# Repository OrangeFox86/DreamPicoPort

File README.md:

# DreamPicoPort (formally DreamcastControllerUsbPico)

Using a Raspberry Pi Pico, DreamPicoPort enables USB interfacing with a Dreamcast or its controllers and peripherals, functioning in either host mode or client mode as depicted below.

Refer to [these instructions](https://github.com/OrangeFox86/DreamPicoPort/wiki/*-Host-Mode-Installation-Guide-(for-use-with-Flycast)) in order to use this with [Hollycast](https://github.com/OrangeFox86/Hollycast) or [flycast](https://github.com/flyinghead/flycast).

| Host Mode | Client Mode |
| -------- | ------- |
|  |  |

This platform may easily be forked and adapted for other interfacing needs. Feel free to do so under the conditions of the supplied [LICENSE.md](LICENSE.md).

Refer to the [releases](https://github.com/OrangeFox86/DreamPicoPort/releases) page for current progress. Refer to the [issues](https://github.com/OrangeFox86/DreamPicoPort/issues) tab for things left to be implemented and known bugs.

---

# General Disclaimer

Proceed at your own risk! I am not liable for any damage that may occur due to the use of any provided schematics, firmware, or any other recommendations made within this project (see [LICENSE.md](LICENSE.md)). There is risk of damage to any attached hardware (ex: USB port, Dreamcast peripheral, or Dreamcast) if circuitry is improperly handled.

---

# Quick Installation Guide

These instructions have been moved to [the wiki](https://github.com/OrangeFox86/DreamPicoPort/wiki/Installation-Guide).

# Build Instructions (for Linux and Windows)

If running under Windows, install [WSL](https://docs.microsoft.com/en-us/windows/wsl/install) and your desired flavor of Linux. I recommend using Ubuntu 22.04 as that is what I have used for development. Then the steps below may be run within your WSL instance.

1. Install git, cmake, and gcc-arm-none-eabi compiler by running the following commands
```bash
sudo apt update
sudo apt -y install git cmake gcc-arm-none-eabi
```

2. (optional) In order to run and debug tests, install standard gcc compilers and gdb by running the following
```bash
sudo apt -y install build-essential gdb
```

3. Clone this repo then cd into the created directory
```bash
git clone https://github.com/Tails86/DreamPicoPort.git
cd DreamPicoPort
```

4. Pull down the pico SDK (this project now uses a fork of the SDK - it will no longer compile under the standard SDK)
```bash
git submodule update --recursive --init
```
Hint: if you have issues building, the easiest way to correct any submodule synchronization issue is to delete the `ext/pico-sdk` directory (ex: `rm -rf ext/pico-sdk`), restore the directory `git restore ext/pico-sdk`, and then re-run the above submodule update command.

5. (optional) Build and run tests - this runs core lib unit tests locally
```bash
./run_tests.sh
```

6. Execute the build script
```bash
./build.sh
```

After build completes, binaries should be located under `dist/`. Pre-built release binaries may be found [here](https://github.com/OrangeFox86/DreamPicoPort/releases).

This project may be opened in vscode. In vscode, the default shortcut `ctrl+shift+b` will build the project. The default shortcut `F5` will run tests with gdb for local debugging. Open the terminal tab after executing tests with debugging to see the results.

---

# Maple Bus Implementation

The Maple Bus is a serial communications protocol which Dreamcast uses to communicate with controllers and other peripherals. Refer to documentation [here](https://dreamcast.wiki/Maple_bus) for general information about the Maple Bus.

## Why the RP2040/RP2350 are Game Changers for Emulating Communication Protocols

To emulate a bespoke communication protocol such as the Maple Bus on an MCU, one would usually either need to add extra hardware or bit bang the interface. This is not true with the RP2040/RP2350 and their PIO. Think of it as several extra small processors on the side using a special machine language purpose-built for handling I/O. This means communication can be offloaded to the PIO and only check on them after an interrupt is activated or a timeout has elapsed. Check out [maple_in.pio](src/hal/MapleBus/maple_in.pio) and [maple_out.pio](src/hal/MapleBus/maple_out.pio) to see the PIO code.

Luckily, the RP2040/RP2350 come with 2 PIO blocks each with 4 separate state machines. This means that the RP2040/RP2350 can easily emulate 4 separate controller interfaces, each at full speed!

## Interfacing with the PIO State Machines

The [MapleBus class](src/hal/MapleBus/MapleBus.hpp) operates as the interface between the microcontroller's code and the PIO state machines, [maple_in.pio](src/hal/MapleBus/maple_in.pio) and [maple_out.pio](src/hal/MapleBus/maple_out.pio).

Using 2 separate PIO blocks for reading and writing is necessary because each PIO block can only hold up to 32 instructions, and this interface is too complex to fit both read and write into a single block. Therefore, the write state machine is completely stopped before starting the read state machine for the targeted bus. Switching state machines is fast enough that there shouldn't be a problem. Testing showed the handoff always occurs within 1 microsecond after bringing the bus back to neutral. A device on the Maple Bus starts responding some time after 50 microseconds from the point of the bus going neutral after an end sequence. This ensures that a response is always captured.

The following lays out the phases of the state machine handled within the MapleBus class.

### PIO Data Handoff

When the write method is called, data is loaded into the Direct Memory Access (DMA) channel designated for use with the maple_out state machine in the MapleBus instance. The DMA will automatically load data onto the TX FIFO of the output PIO state machine so it won't stall waiting for more data.

The first 32-bit word loaded onto the output DMA is how many transmission bits will follow. In order for the state machine to process things properly, `(x - 8) % 32 == 0 && x >= 40` must be true where x is the value of that first 32-bit word i.e. every word is 32 bits long and at least a frame word (32 bits) plus a CRC byte (8 bits) are in the packet. This value needs to be loaded with byte order flipped because byte swap is enabled in the DMA so that all other words are written in the correct byte order. The rest of the data loaded into DMA is the entirety of a single packet as a uint32 array. The last uint32 value holds the 8-bit CRC.

A blocking IRQ is triggered once the maple_out state machine completes the transfer. This then allows MapleBus to stop the maple_out state machine and start the maple_in state machine.

A Direct Memory Access (DMA) channel is setup to automatically pop items off of the RX FIFO of the maple_in state machine so that the maple_in state machine doesn't stall while reading. Once the IRQ is triggered by the maple_in state machine, MapleBus stops the state machine and reads from data in the DMA.

## Generating Maple Bus Output

The [maple_out PIO state machine](src/hal/MapleBus/maple_out.pio) handles Maple Bus output. Data is generated by following the signal definition [here](https://dreamcast.wiki/Maple_bus#Maple_Bus_Signals).

## Sampling Maple Bus Input

The [maple_in PIO state machine](src/hal/MapleBus/maple_in.pio) handles Maple Bus input. Some concessions had to be made in order to handle all input operations within the 32 instruction set limit of the input PIO block. The following are the most notable limitations.
- Only a standard data packet may be sampled
    - The Maple Bus protocol has different types of packets depending on how many times B pulses in the start sequence, but those packets are ignored in this implementation
- The full end sequence is not sampled
    - The packet length in the frame word plus the CRC are relied upon during post-processing in order to verify that the received packet is valid

### Sampling the Start Sequence

The input PIO state machine will wait until **A** transitions LOW and then count how many times **B** toggles LOW then HIGH while making sure **A** doesn't transition HIGH until after **B** transitions HIGH. If the toggle count isn't 4, then the state machine keeps waiting. Otherwise, the state machine signals the application with a non-blocking IRQ and continues to the next phase where data bits are sampled.

### Sampling Data Bits

For each bit, the state machine first waits for the designated clock to be HIGH before proceeding. Then once this line transitions to LOW, the state of the designated data line is sampled. State transitions of the designated data line are ignored except for the case when sensing the end sequence is required as described in the next section.

### Sampling the End Sequence

Whenever **A** is designated as the clock, the input PIO state machine will detect when **B** toggles HIGH then LOW while **A** remains HIGH. It is assumed that this is the beginning of the end sequence since this is not a normal behavior during data transmission. The state machine will then block on an IRQ so that the application can handle the received data.

---

# Appendix A: Abbreviations and Definitions

- `0x` Prefix: The following value is hex format
- Byte: Data consisting of 8 consecutive bits
- DMA: Direct Memory Access
- LSB: Least Significant Byte
- LSb: Least Significant bit
- MSB: Most Significant Byte
- MSb: Most Significant bit
- Nibble: Data consisting of 4 consecutive bits
- PIO: Programmable Input/Output
- SDCK: Serial Data and Clock I/O
- Word: Data consisting of 32 consecutive bits

---

# External Resources

**Maple Bus Resources**

https://archive.org/details/MaplePatent/page/n7/mode/1up

http://mc.pp.se/dc/maplebus.html and http://mc.pp.se/dc/controller.html

https://tech-en.netlify.app/articles/en540236/index.html

https://www.raphnet.net/programmation/dreamcast_usb/index_en.php

https://web.archive.org/web/20100425041817/http://www.maushammer.com/vmu.html

https://hackaday.io/project/170365-blueretro/log/180790-evolution-of-segas-io-interface-from-sg-1000-to-saturn

https://segaretro.org/History_of_the_Sega_Dreamcast/Development

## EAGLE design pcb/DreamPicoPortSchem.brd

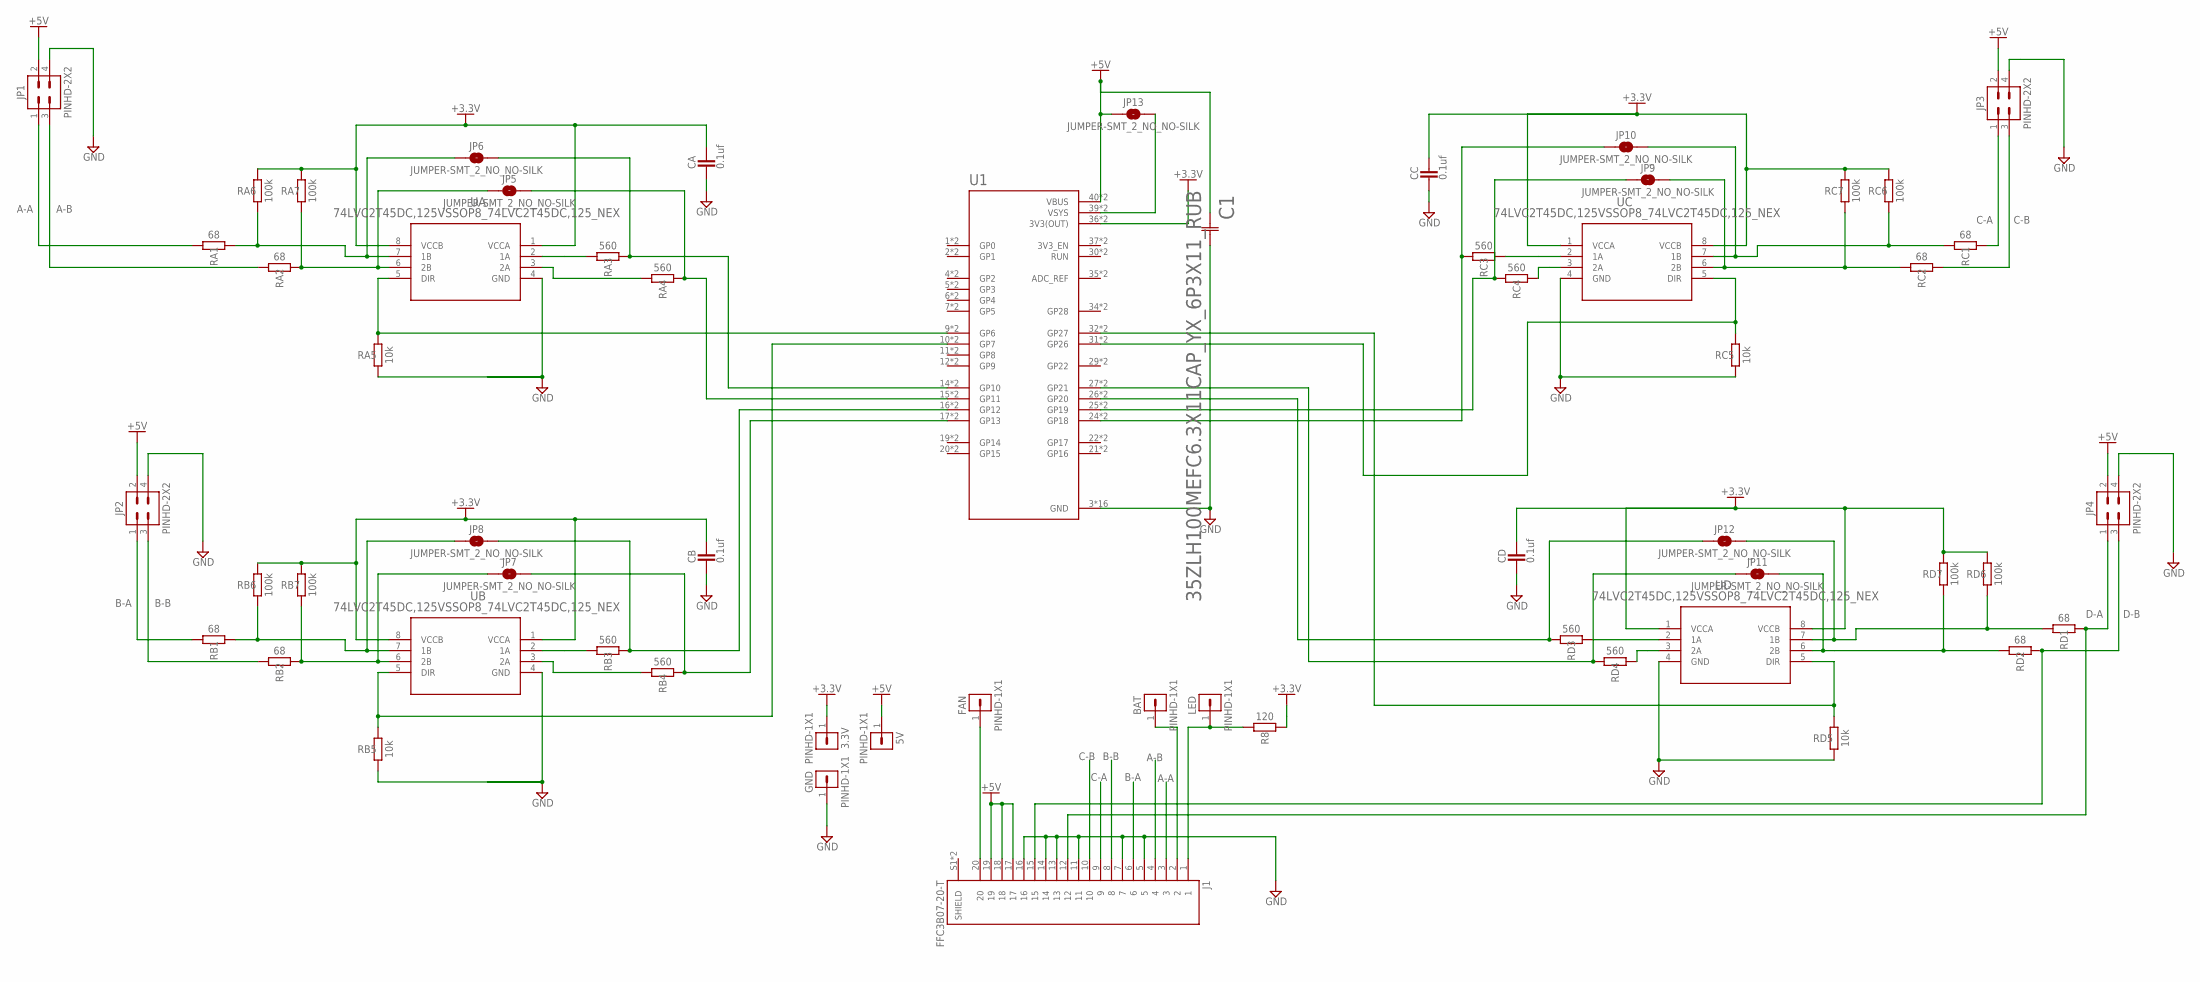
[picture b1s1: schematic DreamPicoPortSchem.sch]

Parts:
3.3V, 5V: PINHD-1X1; 1X01
BAT: PINHD-1X1; 1X01
C1: 35ZLH100MEFC6.3X11CAP_YX_6P3X11_RUB; CAP_YX_6P3X11_RUB
CA: 0.1uf; CAPC1608X85
CB: 0.1uf; CAPC1608X85
CC: 0.1uf; CAPC1608X85
CD: 0.1uf; CAPC1608X85
FAN: PINHD-1X1; 1X01
GND: PINHD-1X1; 1X01
J1: FFC3B07-20-T; GCT_FFC3B07-20-T
JP1, JP2, JP3, JP4: PINHD-2X2; 2X02
JP5, JP6, JP7, JP8, JP9, JP10, JP11, JP12, JP13: JUMPER-SMT_2_NO_NO-SILK; SMT-JUMPER_2_NO_NO-SILK
LED: PINHD-1X1; 1X01
R8: 120; RESC1608X60
RA1, RA2: 68; RESC3216X70
RA3: 560; RESC1608X60
RA4: 560; RESC1608X60; RATING 4
RA5: 10k; RESC1608X60
RA6, RA7: 100k; RESC1608X60
RB1, RB2: 68; RESC3216X70
RB3: 560; RESC1608X60
RB4: 560; RESC1608X60; RATING 4
RB5: 10k; RESC1608X60
RB6, RB7: 100k; RESC1608X60
RC1, RC2: 68; RESC3216X70
RC3, RC4: 560; RESC1608X60
RC5: 10k; RESC1608X60
RC6, RC7: 100k; RESC1608X60
RD1, RD2: 68; RESC3216X70
RD3, RD4: 560; RESC1608X60
RD5: 10k; RESC1608X60
RD6, RD7: 100k; RESC1608X60
U1: RASPBERRY_PICO-NO_DEBUG; PICO-PKG-NO_DEBUG
UA: 74LVC2T45DC,125VSSOP8_74LVC2T45DC,125_NEX; VSSOP8_74LVC2T45DC,125_NEX
UB: 74LVC2T45DC,125VSSOP8_74LVC2T45DC,125_NEX; VSSOP8_74LVC2T45DC,125_NEX
UC: 74LVC2T45DC,125VSSOP8_74LVC2T45DC,125_NEX; VSSOP8_74LVC2T45DC,125_NEX
UD: 74LVC2T45DC,125VSSOP8_74LVC2T45DC,125_NEX; VSSOP8_74LVC2T45DC,125_NEX

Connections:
+3.3V: 3.3V.1, CA.1, CB.1, CC.1, CD.1, R8.1, RA6.2, RA7.2, RB6.2, RB7.2, RC6.2, RC7.2, RD6.2, RD7.2, U1.36 (3V3(OUT)), U1.P$36 (3V3(OUT)), UA.1 (VCCA), UA.8 (VCCB), UB.1 (VCCA), UB.8 (VCCB), UC.1 (VCCA), UC.8 (VCCB), UD.1 (VCCA), UD.8 (VCCB)
+5V: 5V.1, C1.1, J1.17, J1.18, J1.19, JP1.2, JP2.2, JP3.2, JP4.2, JP13.1, U1.40 (VBUS), U1.P$40 (VBUS)
A-A: J1.3, JP1.1, RA1.1
A-B: J1.4, JP1.3, RA2.1
B-A: J1.6, JP2.1, RB1.1
B-B: J1.8, JP2.3, RB2.1
C-A: J1.9, JP3.1, RC1.2
C-B: J1.10, JP3.3, RC2.2
D-A: J1.12, JP4.1, RD1.2
D-B: J1.15, JP4.3, RD2.2
GND: C1.2, CA.2, CB.2, CC.2, CD.2, GND.1, J1.5, J1.7, J1.11, J1.13, J1.14, J1.16, JP1.4, JP2.4, JP3.4, JP4.4, RA5.1, RB5.1, RC5.1, RD5.1, U1.3 (GND), U1.8 (GND), U1.13 (GND), U1.18 (GND), U1.23 (GND), U1.28 (GND), U1.33 (GND), U1.38 (GND), U1.P$3 (GND), U1.P$8 (GND), U1.P$13 (GND), U1.P$18 (GND), U1.P$23 (GND), U1.P$28 (GND), U1.P$33 (GND), U1.P$38 (GND), UA.4 (GND), UB.4 (GND), UC.4 (GND), UD.4 (GND)
unnamed: RA5.2, U1.9 (GP6), U1.P$9 (GP6), UA.5 (DIR)
unnamed: RD3.1, UD.2 (1A)
unnamed: JP6.2, RA3.1, U1.14 (GP10), U1.P$14 (GP10)
unnamed: RB3.2, UB.2 (1A)
unnamed: RA4.2, UA.3 (2A)
unnamed: JP5.1, RA2.2, RA7.1, UA.6 (2B)
unnamed: JP6.1, RA1.2, RA6.1, UA.7 (1B)
unnamed: RC5.2, U1.31 (GP26), U1.P$31 (GP26), UC.5 (DIR)
unnamed: FAN.1, J1.20
unnamed: BAT.1, J1.2
unnamed: JP10.1, RC3.2, U1.24 (GP18), U1.P$24 (GP18)
unnamed: RB5.2, U1.10 (GP7), U1.P$10 (GP7), UB.5 (DIR)
unnamed: JP8.2, RB3.1, U1.16 (GP12), U1.P$16 (GP12)
unnamed: RD4.1, UD.3 (2A)
unnamed: JP7.2, RB4.1, U1.17 (GP13), U1.P$17 (GP13)
unnamed: RB4.2, UB.3 (2A)
unnamed: J1.1, LED.1, R8.2
unnamed: JP8.1, RB1.2, RB6.1, UB.7 (1B)
unnamed: JP7.1, RB2.2, RB7.1, UB.6 (2B)
unnamed: RA3.2, UA.2 (1A)
unnamed: JP5.2, RA4.1, U1.15 (GP11), U1.P$15 (GP11)
unnamed: JP9.1, RC4.2, U1.25 (GP19), U1.P$25 (GP19)
unnamed: RC4.1, UC.3 (2A)
unnamed: JP13.2, U1.39 (VSYS), U1.P$39 (VSYS)
unnamed: JP10.2, RC1.1, RC6.1, UC.7 (1B)
unnamed: JP9.2, RC2.1, RC7.1, UC.6 (2B)
unnamed: RC3.1, UC.2 (1A)
unnamed: JP12.1, RD3.2, U1.26 (GP20), U1.P$26 (GP20)
unnamed: JP11.1, RD4.2, U1.27 (GP21), U1.P$27 (GP21)
unnamed: RD5.2, U1.32 (GP27), U1.P$32 (GP27), UD.5 (DIR)
unnamed: JP12.2, RD1.1, RD6.1, UD.7 (1B)
unnamed: JP11.2, RD2.1, RD7.1, UD.6 (2B)

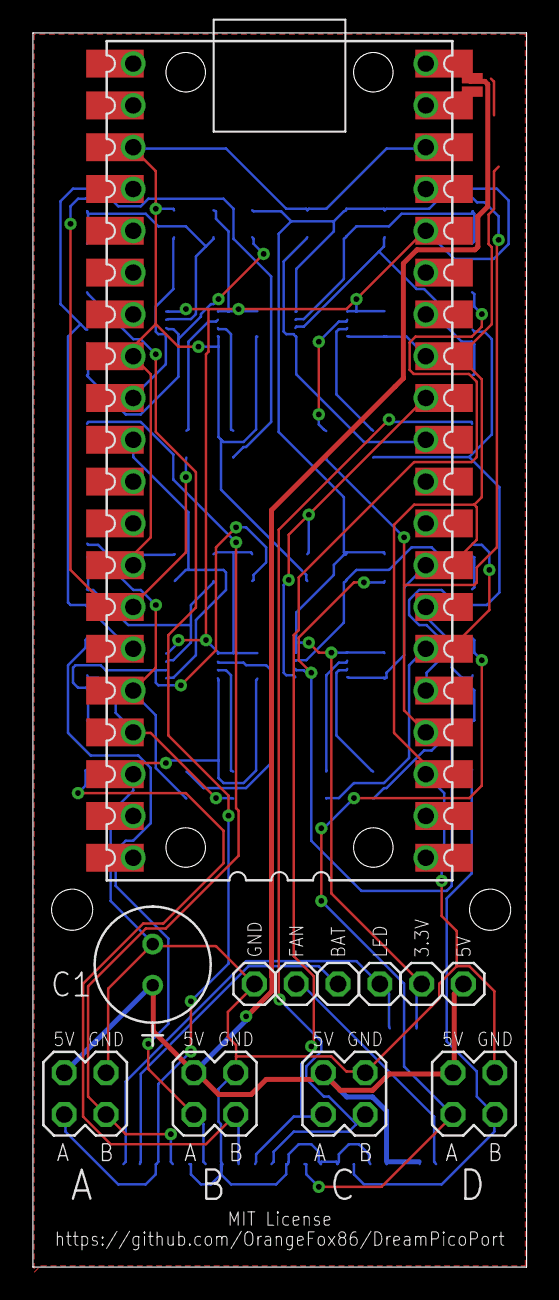
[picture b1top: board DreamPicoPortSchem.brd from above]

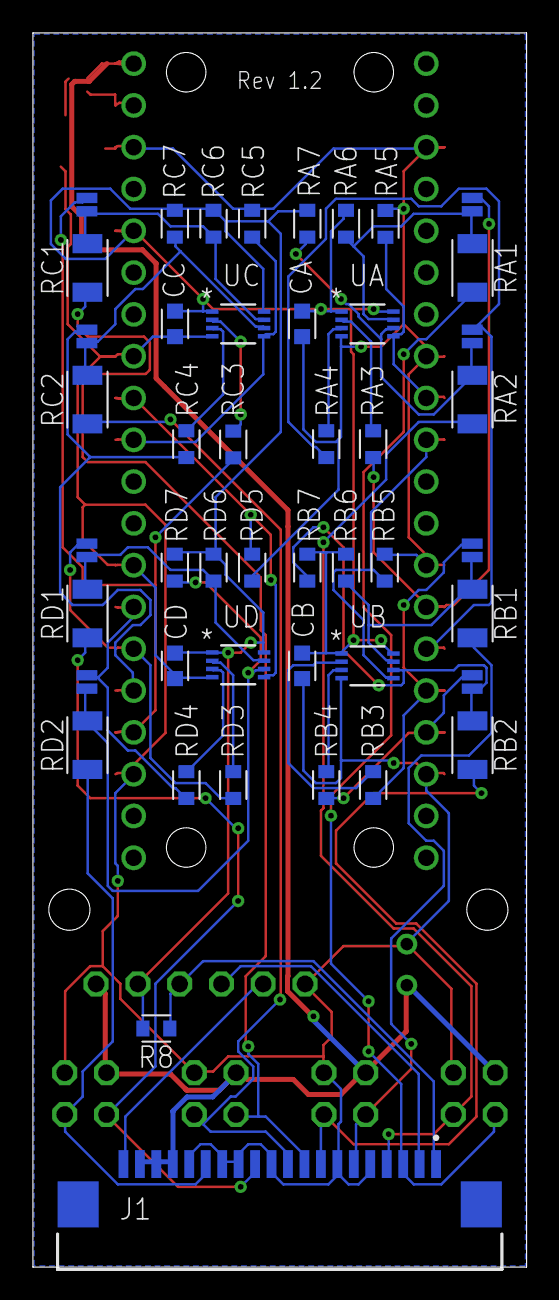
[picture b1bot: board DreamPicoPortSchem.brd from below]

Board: 2 copper layers, 30.0 x 75.0 mm, 59 parts (46 on the bottom side), 43 nets.

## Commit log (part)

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2025-03-04 Increased max failure disconnect count to 10
2025-03-04 Fixed unit test
2025-03-05 Revert "Serialize most responses from flycast command parser"
    This reverts commit 27688ca25abe4ae2d669cafbf73ca31d58d22dc8.
2025-03-05 Added missing newline
2025-03-05 Revert "Added missing newline"
    This reverts commit 00a7efec36e1c7176462fe65b3704ba69ed755c6.
2025-03-05 Revert "Revert "Serialize most responses from flycast command parser""
    This reverts commit 31c04622a08e7f513342aa6a0d10822cc4626b24.
2025-03-07 Save last screen set through FlycastCommandParser
2025-03-08 Change the output of X? because it was difficult to parse
2025-03-08 Fixed unit tests
2025-03-30 Added zero build configuration
2025-03-30 Removed asterisk from zero_host-4p.uf2
2025-03-30 Removed installation instructions from the README since they now exist in the wiki
2025-03-31 Added RP2350 to README
2025-04-01 updated pico-sdk
2025-04-19 175: Added board version label
2025-05-04 175 upload board files (#176)
    Added PCB board files
    ---------
2025-05-26 178: Increase CPU freq when pico2 used
2025-05-26 178 minor improvements (#179)
    * 178: Increase CPU freq when pico2 used
    * 178: Fixed USB_CDC_ENABLED and added USB_MSC_ENABLED
    ---------
2025-06-09 177: Mask vias on PCB
2025-06-15 177: Added board examples
2025-07-14 183: First attempt at integrating WebUSB - connection issues
2025-07-16 183: This gets enumerated by Windows, but WebUSB is not enabled
2025-07-17 183: WebUSB interface works!
2025-07-20 183: Reorganized webusb processing into its own file
2025-08-03 183: Added parser for Flycast into webusb
2025-08-03 183: Fixed webusb connection issues
2025-08-03 183: Enable 2 WebUSB interfaces
2025-08-05 183: Set unique device GUIDs; fixed webusb packet parsing
2025-08-06 183: Fixed return packet size
2025-08-06 183: Swap bytes on received maple packet
2025-08-06 Revert "183: Swap bytes on received maple packet"
    This reverts commit 66862aeb306b2d934189ed770c4dfc0cffd63f72.
2025-08-07 183: Allow the MapleBus object to automatically adjust to tx/rx byte order and use NETWORK order in Maple passthrough parsers
2025-08-07 183: Refactoring
2025-08-10 183: Peripheral summary is presented in a binary token stream instead of ASCII
2025-08-10 183: Corrected compile warning
2025-08-12 183: Added settings load-from/save-to flash
2025-08-12 183: Added settings WebUsb parser
2025-08-14 183: Added interfaces where each player can be independently enabled/disabled
2025-08-16 183: Added another type of dynamic auto detect
2025-08-17 183: Delay for up to 3.5 seconds on first boot if no devices are detected - this ensures USB is not connecting/disconnecting/connecting every time it boots if dynamic connection is selected
2025-08-17 183: More refactoring of host.cpp
2025-08-17 183: Renamed files so it's apparent where main() lives; moved host setup functionality into its own module
2025-08-17 183: Simplification
2025-08-19 183: Added commands to the settings WebUSB parser and removed the number of player variants of binary
2025-08-21 183: Very rough and basic webusb page
2025-08-21 183: Set temporary webusb_url
2025-08-22 183: Fixed CRC computation in returned packet and updated webusb application to display parsed data on console
2025-08-23 183: Add a short delay to selecting a tab
2025-08-23 183: Try onpageshow instead of onpagereveal
2025-08-23 183: Try just executing function
2025-08-23 183: Added the beginnings of state machine(s) to the web page
2025-08-23 183: GitHub requires web content to be under a folder called docs
2025-08-23 183: Move webusb page to a new folder to leave room for future content
2025-08-23 183: Add detection for WebUSB and display error if browser isn't supported
2025-08-24 183: Removed the connect button and replaced with a select button - connection is only established while a state machine is running
2025-08-24 183: Some fixes and buildout of webpage
2025-08-24 183: Test code
2025-08-24 183: Rough VMU read implementation (not completely working)
2025-08-24 183: Added development messages which I will remove once complete
2025-08-24 183: Show device selection dialog when no devices detected
2025-08-24 183: Gray out content until device is selected
2025-08-24 183: Split up buffer consuming from data processing in WebUSB parser so that processing may happen on the maple core
2025-08-25 183: Finished off read VMU function and polished up some of the display components
2025-08-25 183: Finished write to VMU over WebUSB
2025-08-26 183: Begin to fill out GPIO settings load
2025-08-26 183: Optimize by using time_us_32() when absolute time isn't needed
2025-08-26 183: Fixed edge case by clearing out watchdog scratch values after they are no longer needed
2025-08-26 DIR gpio is allowed to be negative while player is enabled
2025-08-27 183: Completed setting GPIO over WebUSB
2025-08-27 183: Set default settings on page after all settings are reset; fixed reboot issues regarding USB after settgins are updated
2025-08-30 183: Roughly handle default settings generation for zero_host.uf2
2025-08-30 183: Removed code that shouldn't have been pushed
2025-08-30 183: Can now retrieve controller state though USB
2025-08-30 183: Reduce potential frequent reallocations
2025-08-31 183: Minor tweaks
2025-08-31 183: Always call reset() and then close() on device regardless if the controlTransferOut() succeeds or not
2025-08-31 Process received data before doing another read loop
2025-09-01 183: Allow the WebUSB announcement to be disabled
2025-09-01 183: Added context to why the checkbox is included
2025-09-01 183: Add detection for reboot due to USB command
2025-09-01 183: Added special failure handling for Android
2025-09-02 183: Always include serial with interface string
2025-09-02 183: Go back to reboot for MacOS and tweaked USB restart features
2025-09-06 183: Corrected indexing issues when the set of connected controllers are not contiguous or not starting from 0
2025-09-06 183: Committing missing file
2025-09-06 183: Added XO command which will provide information about what gamepads are available and which are connected; only auto setting should cause disconnect
2025-09-13 185: Corrected buffer increment issue
2025-09-27 Bump USB version to 1.2.1
2025-10-07 Added comments to help ensure vendor interfaces don't change in the future
2025-10-07 Added what these interfaces must handle
2025-10-07 Added comments to help ensure vendor interfaces don't change in the future (#189)
    * Added comments to help ensure vendor interfaces don't change in the future
    * Added what these interfaces must handle
    * Added comment about what the settings web page uses
    ---------
2025-11-24 Added 3D objects for case (#191)
2025-11-30 190: Added debug build and launch/attach configurations
2025-11-30 190: Prvent WebUsbInterface::vendorWrite() from looping forever
2025-12-01 190: Bump version to 1.2.2
2025-12-06 Added button to get device information
2025-12-06 Refactored state machine layout: removed cancel and timeout and replaced with optional done function; added name since most don't need to implement done
2025-12-06 Refactoring: Moved all state machines into defined classes
2025-12-07 Fixed stress test labels
2025-12-07 Add test tab to settings in WebUSB (#195)
    Added test tab to settings in WebUSB page
2025-12-07 Fixed issues with tests
2025-12-07 Cleaned up profiler
2025-12-07 Fixed tests
2025-12-07 Added note on WebUSB page and update link if older firmware detected
2025-12-07 On WebUSB page: added note about not running flycast and update link (#199)
    On WebUSB page: added note about not running flycast and update link
2025-12-20 200: Add VMU beep to basic test
2025-12-20 200: Removed unnecessary {}
2025-12-20 200: Added note on settings load when some settings not available
2025-12-20 200: Corrected unit test
2025-12-20 197: Clear write buffer on WinUSB/WebUSB connect/disconnect
2025-12-21 197: Cache last received release tag
2025-12-21 197: Optionally send back a framing command on connect
2025-12-21 197: Force purge of last command upon connection
2025-12-21 197: Several tweaks
2025-12-21 197: Added connect value 3
2025-12-21 197: Add a longer boot delay which helps if the clock on the pico is malfunctioning
2025-12-21 197 if outgoing vendor buffer is not empty on disconnect this causes issues on next connection (#202)
    - Clear outgoing buffer on connection/disconnection events
    - Send a bunch of zeros to ensure any command stuck in the endpoint is shifted out on the host
    - Added exception handler when not debug
    - Added watchdog timeout
    - Added a system WebUSB processor with an echo command - I think this could be used to send a random value and ensure the random value is echoed upon connection
    - Connection value of 2 will send back a null command to potentially help with connection
2025-12-21 Delay processing read data for 25 ms after connection (#203)
2025-12-25 Simplified and fixed watchdog logic (was resetting if any core signaled instead of ALL)
2025-12-25 Simplified and fixed watchdog logic (was resetting if any core signaled instead of ALL) (#205)
2025-12-25 204: Don't try to reaquire lock
2025-12-27 204: Keep holding onto the lock while buffers are being manipulated in process()
2026-01-03 204: Added callback feature to MapleBus
2026-01-03 204: Moved all USB operations to core 0
2026-01-04 204: Ensure vendor write happens only on core 0; fixed unit tests
2026-01-04 204: Removed unnecessary changes
2026-01-04 204: Ensure button 21 is emitted on button press events
2026-01-04 204: Removed unnecessary change
2026-01-05 208: Enforce a 1 ms gap between writes to Maple Bus
2026-02-21 Revert "Revert "208: Enforce a 1 ms gap between writes to Maple Bus""
    This reverts commit 78cacb827aeaaacc51491df99044597d26328f43.
2026-02-21 208: Downgrade to pico-sdk 2.1.1
2026-03-15 208: Reduce number of logical branches in the timeout case of the Maple Bus state machine
2026-03-15 208: Updated copyright statements
2026-03-15 208: HTML hover tooltip will work when hovering over the label now too
2026-03-15 Revert "Revert "Revert "208: Enforce a 1 ms gap between writes to Maple Bus"""
    This reverts commit a65cb3a36f6fec77aa286d01027de68e5e11319d.
2026-03-15 Version 1.2.3
2026-03-15 215: Parse real version in settings webpage
2026-03-16 Updated 5V to VBUS on PCB
2026-03-23 Added MapleBus status command
2026-04-30 Fixed diagnostics generation and added Get Diagnostics button to setting web page
2026-04-30 Hide the 'Get Diagnostics' button when version is less than 1.2.4
2026-04-30 Corrected PR issues
2026-04-30 Added missing comma
2026-05-24 Move diagnostics time retrieval to after diagnostics are retrieved, ensuring all timestamps will be in the past
2026-05-24 Show link when SecurityError is encountered in linux
2026-05-24 Add cancel call
2026-05-24 Tweaked message
2026-06-16 Fixed function code to hex conversion and added fn names 'Ext Storage' and 'Camera'
2026-06-16 Fixed function code to hex conversion and added fn names 'Ext Storage' and 'Camera' (#222)
2026-06-20 Avoid double reboot when settings applied with auto detect selected (#223)
2026-06-22 Use minimum analog value of -128 - this fixes SDL trigger interaction issue (#224)
2026-06-23 Update links to host mode setup guide
2026-06-23 Update links to host mode setup guide (#226)
2026-06-27 227: Fixed volatile to non-volatile copy
2026-06-27 227: Reduce number of duplicate actions by only running as part of PR or push to main

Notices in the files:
pcb/DreamPicoPortSchem.brd:
MIT License
parts and their libraries:
SparkFun-Jumpers: Licensing: Creative Commons ShareAlike 4.0 International - https://creativecommons.org/licenses/by-sa/4.0
COPYRIGHT: Copyright (C) 2025 Ultra Librarian. All rights reserved.
